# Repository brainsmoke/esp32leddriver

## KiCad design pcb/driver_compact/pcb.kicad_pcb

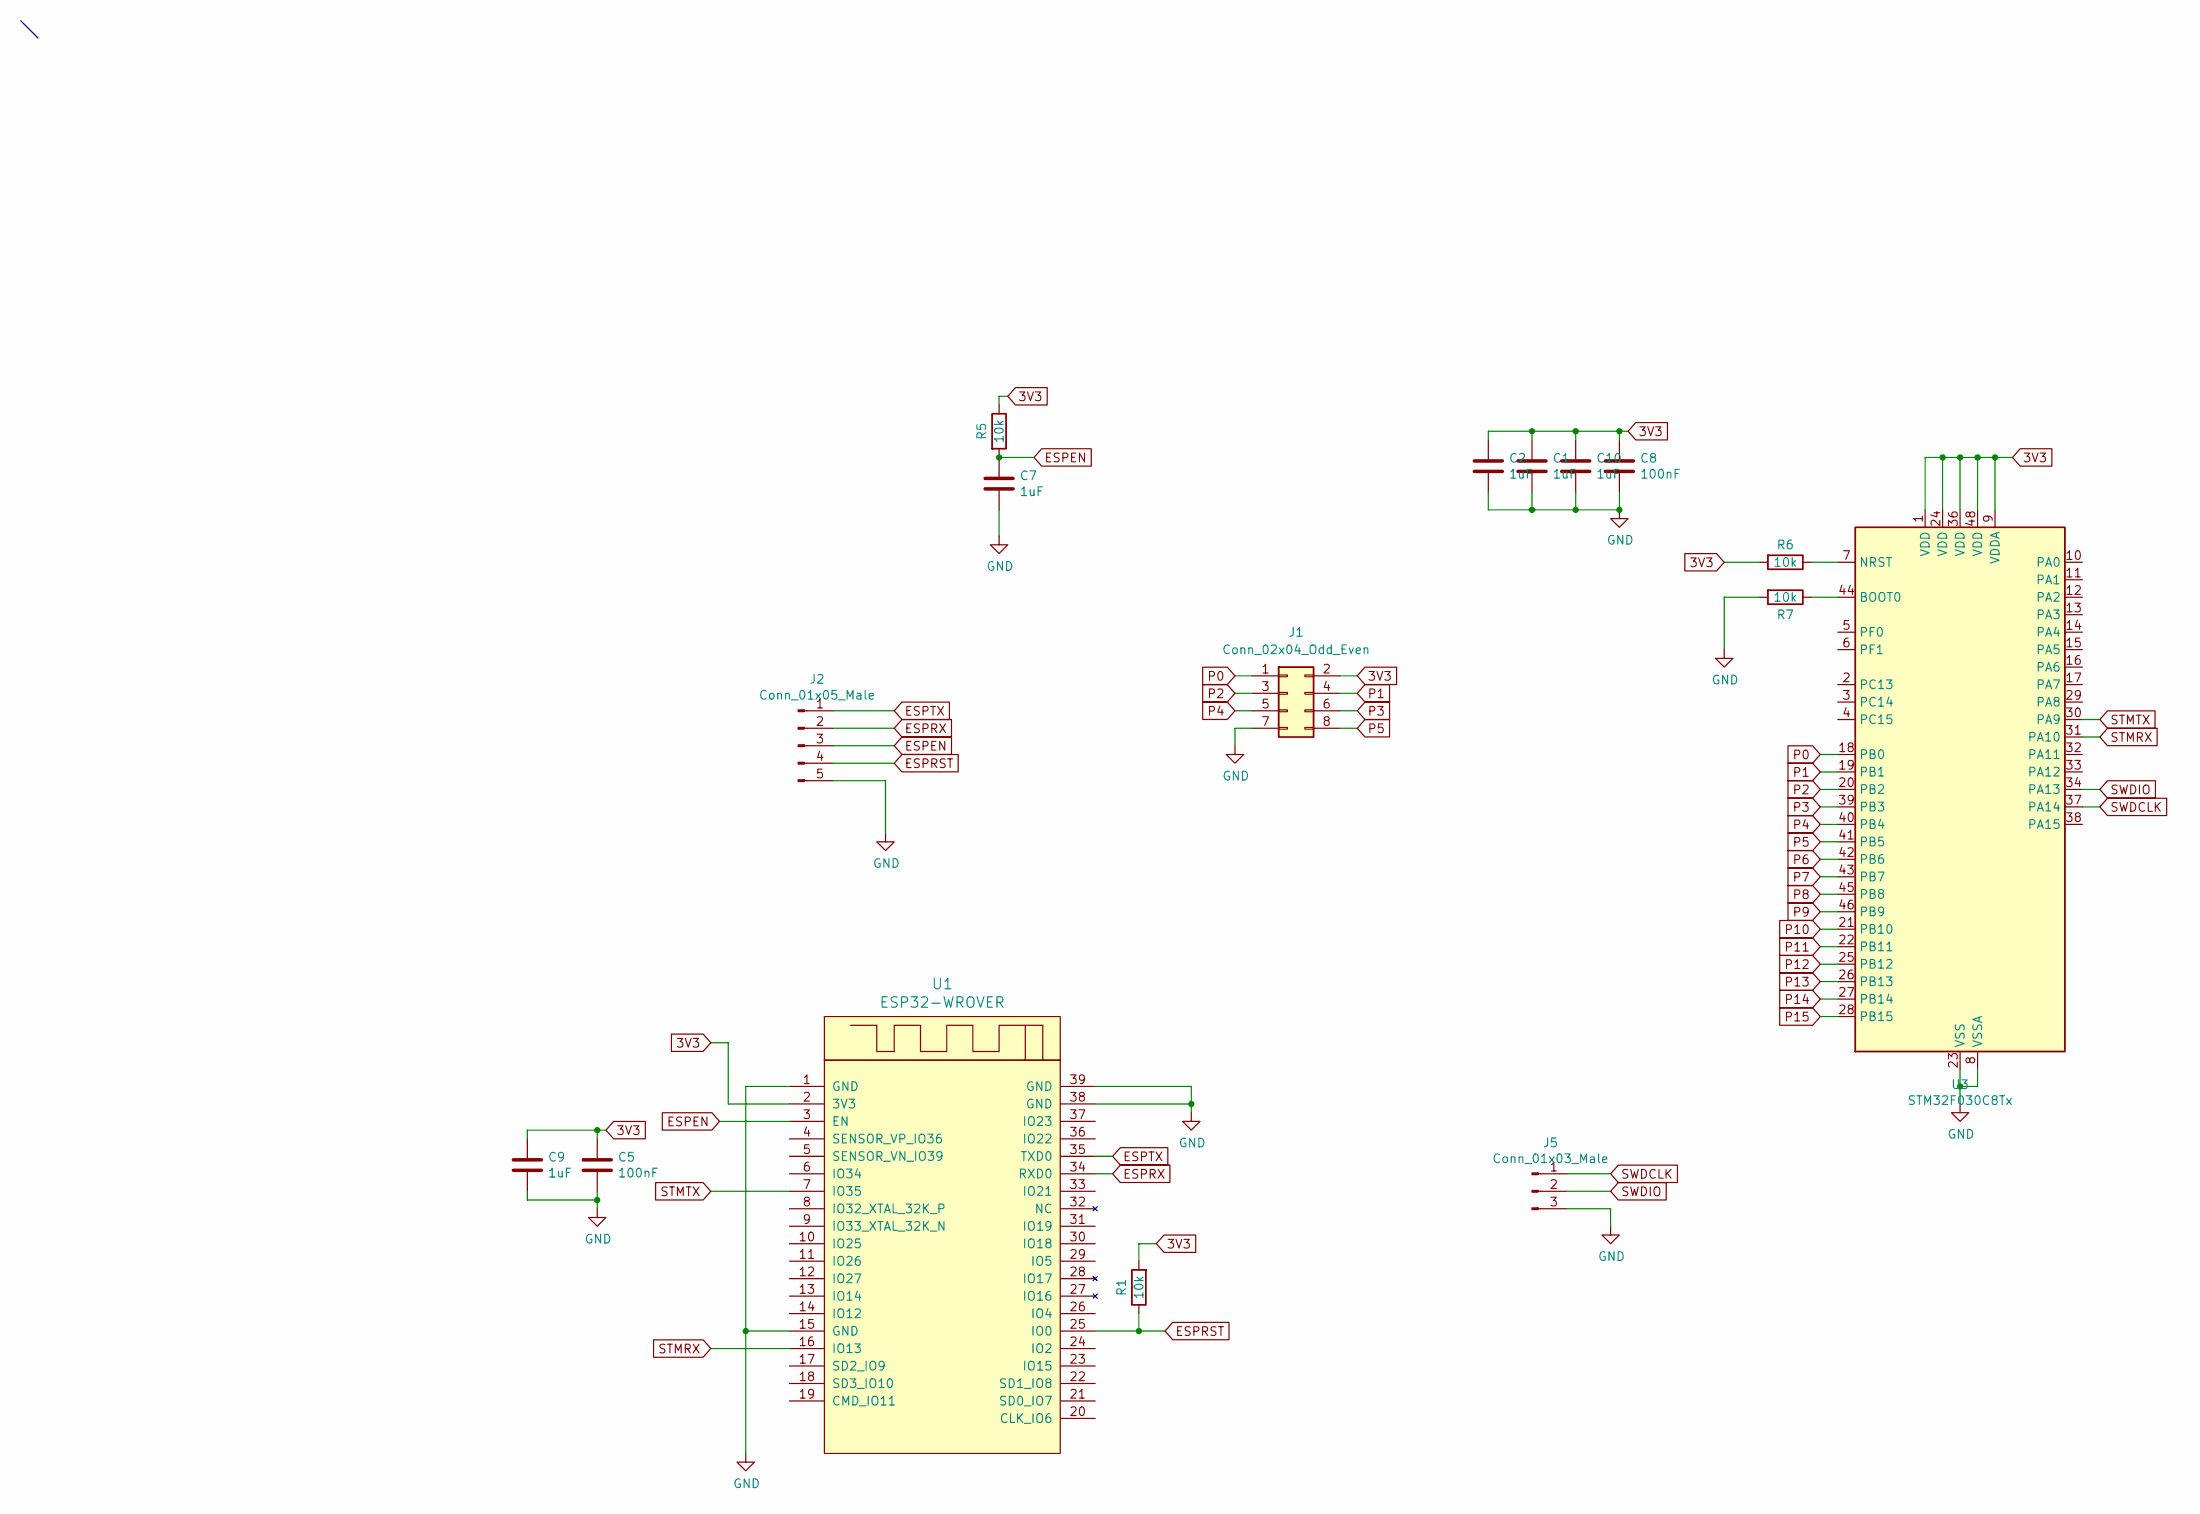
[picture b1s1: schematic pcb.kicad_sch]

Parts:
C1, C2, C7, C9, C10: 1uF; C_0402_1005Metric; LCSC C52923
C5, C8: 100nF; C_0402_1005Metric; LCSC C1525
J1: Conn_02x04_Odd_Even; PinSocket_2x04_P2.54mm_Vertical
J2: Conn_01x05_Male; Molex_PicoBlade_53261-0571_1x05-1MP_P1.25mm_Horizontal; LCSC C225114
J5: Conn_01x03_Male; PinHeader_1x03_P2.54mm_Vertical
R1, R5, R6, R7: 10k; R_0402_1005Metric; LCSC C25744
U1: ESP32-WROVER; XCVR_ESP32-WROVER; LCSC C701352
U3: STM32F030C8Tx; LQFP-48_7x7mm_P0.5mm; LCSC C23922

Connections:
3V3: C1.1, C2.1, C5.1, C8.1, C9.1, C10.1, J1.2, R1.2, R5.1, R6.2, U1.2 (3V3), U3.1 (VDD), U3.9 (VDDA), U3.24 (VDD), U3.36 (VDD), U3.48 (VDD)
ESPEN: C7.1, J2.3, R5.2, U1.3 (EN)
ESPRST: J2.4, R1.1, U1.25 (IO0)
ESPRX: J2.2, U1.34 (RXD0)
ESPTX: J2.1, U1.35 (TXD0)
GND: C1.2, C2.2, C5.2, C7.2, C8.2, C9.2, C10.2, J1.7, J2.5, J5.3, R7.2, U1.1 (GND), U1.15 (GND), U1.38 (GND), U1.39 (GND), U3.8 (VSSA), U3.23 (VSS), U3.35 (VSS), U3.47 (VSS)
unnamed: R7.1, U3.44 (BOOT0)
unnamed: R6.1, U3.7 (NRST)
P0: J1.1, U3.18 (PB0)
P1: J1.4, U3.19 (PB1)
P2: J1.3, U3.20 (PB2)
P3: J1.6, U3.39 (PB3)
P4: J1.5, U3.40 (PB4)
P5: J1.8, U3.41 (PB5)
P6: U3.42 (PB6)
P7: U3.43 (PB7)
P8: U3.45 (PB8)
P9: U3.46 (PB9)
P10: U3.21 (PB10)
P11: U3.22 (PB11)
P12: U3.25 (PB12)
P13: U3.26 (PB13)
P14: U3.27 (PB14)
P15: U3.28 (PB15)
STMRX: U1.16 (IO13), U3.31 (PA10)
STMTX: U1.7 (IO35), U3.30 (PA9)
SWDCLK: J5.1, U3.37 (PA14)
SWDIO: J5.2, U3.34 (PA13)

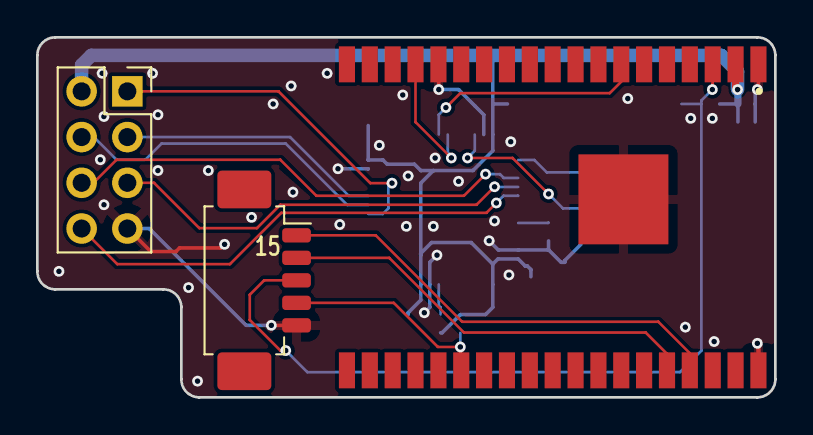
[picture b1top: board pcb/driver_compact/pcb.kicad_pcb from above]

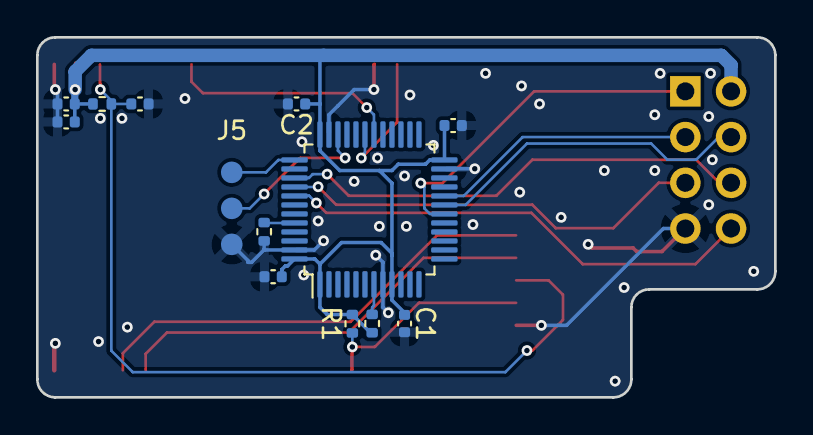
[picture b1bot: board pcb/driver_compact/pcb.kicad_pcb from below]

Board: 4 copper layers, 41.0 x 20.0 mm, 16 parts (13 on the bottom side), 18 nets.

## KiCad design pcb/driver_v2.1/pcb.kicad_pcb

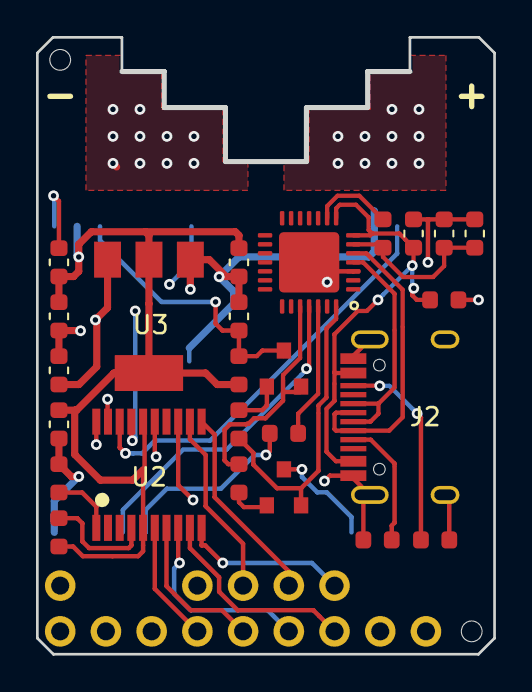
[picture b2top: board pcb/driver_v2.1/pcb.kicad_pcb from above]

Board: 4 copper layers, 25.4 x 34.3 mm, 29 parts (1 on the bottom side), 33 nets.

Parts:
C1, C6, C7: 1uF; C_0603_1608Metric
C2, C4, C9: 10uF; C_0603_1608Metric
C3, C5, C8: 100nF; C_0603_1608Metric
J1: Conn_01x08_Male; PinHeader_1x08_P2.54mm_Vertical
J2: USB_C_Receptacle_USB2.0; USB_C_Receptacle_HRO_TYPE-C-31-M-12
J3: Conn_01x04_Male; PinHeader_1x04_P2.54mm_Vertical
J4: Conn_01x02_Male; PinHeader_1x02_P2.54mm_Vertical
Q1, Q2: AO3400; SOT-23
R1: 1k; R_0603_1608Metric_nolabel
R2, R3, R4, R5, R6, R7: 10k; R_0603_1608Metric_nolabel
R8, R9: 5.1k; R_0603_1608Metric_nolabel
R10: 0Ohm; R_0603_1608Metric_nolabel
U1: ESP32-WROVER; XCVR_ESP32-WROVER
U2: STM32F030F4Px; TSSOP-20_4.4x6.5mm_P0.65mm
U3: AMS1117-3.3; SOT-223-3_TabPin2
U4: CP2102N-Axx-xQFN28; QFN-28-1EP_5x5mm_P0.5mm_EP3.35x3.35mm

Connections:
3V3: C4.1, C5.1, C8.1, C9.1, R5.1, R6.2, U1.2 (3V3), U2.5 (VDDA), U2.16 (VDD), U3.2 (VO)
+5V: C2.1, J1.7, J1.8, R10.2, U3.3 (VI)
ESPEN: C7.1, Q1.3 (D), R5.2, U1.3 (EN)
ESPRST: Q2.3 (D), U1.25 (IO0)
ESPRX: R1.1, U1.34 (RXD0)
ESPTX: U1.35 (TXD0), U4.25 (RXD)
GND: C1.2, C2.2, C3.2, C4.2, C5.2, C6.2, C7.2, C8.2, C9.2, J1.1, J1.2, J2.A1 (GND), J2.A12 (GND), J2.B1 (GND), J2.B12 (GND), J2.S1 (SHIELD), R7.2, R8.1, R9.1, U1.1 (GND), U1.15 (GND), U1.38 (GND), U1.39 (GND), U2.15 (VSS), U3.1 (GND), U4.3 (GND), U4.29 (GND)
unnamed: J1.3, U2.6 (PA0)
unnamed: J1.4, U2.7 (PA1)
unnamed: J1.5, U2.8 (PA2)
unnamed: J1.6, U2.9 (PA3)
unnamed: J2.A5 (CC1), R8.2
unnamed: J2.B5 (CC2), R9.2
unnamed: J3.1, U2.13 (PA7)
unnamed: J3.2, U2.12 (PA6)
unnamed: J3.3, U2.11 (PA5)
unnamed: J3.4, U2.10 (PA4)
unnamed: Q1.1 (G), R3.1
unnamed: Q1.2 (S), R4.2, U4.24 (~RTS)
unnamed: Q2.1 (G), R4.1
unnamed: Q2.2 (S), R3.2, U4.28 (~DTR)
unnamed: R7.1, U2.1 (BOOT0)
unnamed: R6.1, U2.4 (NRST)
unnamed: J2.A6 (D+), J2.B6 (D+), U4.4 (D+)
unnamed: J2.A7 (D-), J2.B7 (D-), U4.5 (D-)
unnamed: R1.2, U4.26 (TXD)
unnamed: C1.1, J2.A4 (VBUS), J2.A9 (VBUS), J2.B4 (VBUS), J2.B9 (VBUS), R10.1, U4.7 (VREGIN), U4.8 (VBUS)
unnamed: R2.2, U4.9 (~RST)
STMRX: U1.16 (IO13), U2.18 (PA10)
STMTX: U1.7 (IO35), U2.17 (PA9)
SWDCLK: J4.2, U2.20 (PA14)
SWDIO: J4.1, U2.19 (PA13)
VIO: C3.1, C6.1, R2.1, U4.6 (VDD)

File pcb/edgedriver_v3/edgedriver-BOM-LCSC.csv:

Comment,Designator,Footprint,LCSC Part Number
"10uF","C4,C2,C9","0603","C19702"
"1uF","C7,C6,C1","0603","C15849"
"100nF","C8,C5,C3","0603","C14663"
"AO3400","Q1,Q2","SOT-23-3L","C20917"
"1k","R1","0603","C21190"
"10k","R6,R7,R3,R4,R5,R2","0603","C25804"
"STM32F030F4P6","U2","TSSOP-20_4.4x6.5x0.65P","C89040"
"AMS1117-3.3","U3","SOT-223","C6186"
"CP2104","U4","QFN-24_EP_4.0x4.0x0.5P","C47742"

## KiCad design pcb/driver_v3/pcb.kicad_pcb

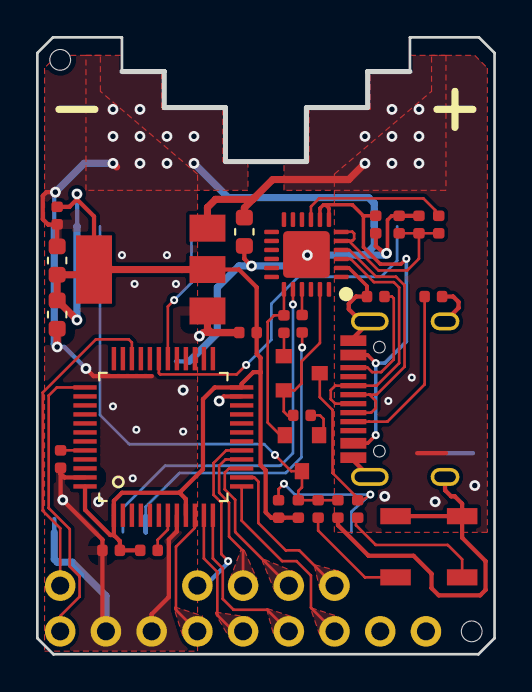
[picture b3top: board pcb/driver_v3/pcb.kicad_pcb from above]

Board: 4 copper layers, 25.4 x 34.3 mm, 34 parts (1 on the bottom side), 35 nets.

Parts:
C1, C6, C7: 1uF; C_0402_1005Metric
C2, C4, C9: 10uF; C_0603_1608Metric
C3, C5, C8, C10: 100nF; C_0402_1005Metric
J1: Conn_01x08_Male; PinHeader_1x08_P2.54mm_Vertical
J2: USB_C_Receptacle_USB2.0; USB_C_Receptacle_HRO_TYPE-C-31-M-12
J3: Conn_01x04_Male; PinHeader_1x04_P2.54mm_Vertical
J4: Conn_01x02_Male; PinHeader_1x02_P2.54mm_Vertical
Q1, Q2: AO3400; SOT-23
R1: 1k; R_0402_1005Metric
R2, R3, R4, R5, R6, R7, R11: 10k; R_0402_1005Metric
R8, R9: 5.1k; R_0402_1005Metric
R10, R12: 470 Ohm; R_0402_1005Metric
SW1, SW2: SW_SPST; SW_SPST_B3U-1000P
U1: ESP32-WROVER; XCVR_ESP32-WROVER
U2: STM32F030C8Tx; LQFP-48_7x7mm_P0.5mm
U3: AMS1117-3.3; SOT-223-3_TabPin2
U4: CP2104; QFN-24-1EP_4x4mm_P0.5mm_EP2.6x2.6mm

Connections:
3V3: C4.1, C5.1, C8.1, C9.1, C10.1, R5.1, R6.2, R11.1, U1.2 (3V3), U2.1 (VDD), U2.9 (VDDA), U2.24 (VDD), U2.48 (VDD), U3.2 (VO)
+5V: C2.1, J1.7, J1.8, U3.3 (VI)
ESPEN: C7.1, Q1.3 (D), R5.2, R10.1, U1.3 (EN)
ESPRST: Q2.3 (D), R11.2, R12.1, U1.25 (IO0)
ESPRX: R1.1, U1.34 (RXD0)
ESPTX: U1.35 (TXD0), U4.20 (RXD)
GND: C1.2, C2.2, C3.2, C4.2, C5.2, C6.2, C7.2, C8.2, C9.2, C10.2, J1.1, J1.2, J2.A1 (GND), J2.A12 (GND), J2.B1 (GND), J2.B12 (GND), J2.S1 (SHIELD), R7.2, R8.1, R9.1, SW1.2 (B), SW2.2 (B), U1.1 (GND), U1.15 (GND), U1.38 (GND), U1.39 (GND), U2.8 (VSSA), U2.23 (VSS), U2.47 (VSS), U3.1 (GND), U4.2 (GND), U4.25 (GND)
unnamed: J1.3, U2.10 (PA0)
unnamed: J1.4, U2.11 (PA1)
unnamed: J1.5, U2.12 (PA2)
unnamed: J1.6, U2.13 (PA3)
unnamed: J2.A5 (CC1), R8.2
unnamed: J2.B5 (CC2), R9.2
unnamed: J3.1, U2.17 (PA7)
unnamed: J3.2, U2.16 (PA6)
unnamed: J3.3, U2.15 (PA5)
unnamed: J3.4, U2.14 (PA4)
unnamed: Q1.1 (G), R3.1
unnamed: Q1.2 (S), R4.2, U4.19 (~RTS)
unnamed: Q2.1 (G), R4.1
unnamed: Q2.2 (S), R3.2, U4.23 (~DTR)
unnamed: R10.2, SW1.1 (A)
unnamed: R12.2, SW2.1 (A)
unnamed: R7.1, U2.44 (BOOT0)
unnamed: R6.1, U2.7 (NRST)
unnamed: J2.A6 (D+), J2.B6 (D+), U4.3 (D+)
unnamed: J2.A7 (D-), J2.B7 (D-), U4.4 (D-)
unnamed: C1.1, J2.A4 (VBUS), J2.A9 (VBUS), J2.B4 (VBUS), J2.B9 (VBUS), U4.7 (REGIN), U4.8 (VBUS)
unnamed: R1.2, U4.21 (TXD)
unnamed: R2.2, U4.9 (~RST)
STMRX: U1.16 (IO13), U2.31 (PA10)
STMTX: U1.7 (IO35), U2.30 (PA9)
SWDCLK: J4.2, U2.37 (PA14)
SWDIO: J4.1, U2.34 (PA13)
VIO: C3.1, C6.1, R2.1, U4.5 (VIO), U4.6 (VDD)

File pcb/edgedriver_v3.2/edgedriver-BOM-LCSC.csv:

Comment,Designator,Footprint,LCSC Part Number
"10uF","C4,C2,C9","0603","C19702"
"1uF","C7,C6,C1","0402","C52923"
"100nF","C8,C5,C3,C10","0402","C1525"
"USB_C_Receptacle_USB2.0","J2","TYPE-C-31_L8.94_W7.3","C165948"
"AO3400","Q1,Q2","SOT-23-3L","C20917"
"1k","R1","0402","C11702"
"470 Ohm","R10,R12","0402","C25167"
"10k","R6,R7,R3,R4,R5,R2,R11","0402","C25744"
"5.1k","R8,R9","0402","C25905"
"SW_SPST","SW1,SW2","Button_Switch_SMD:SW_Push_1P1T_NO_CK_KMR2","C318893"
"STM32F030C8T6","U2","LQFP-48_7.0x7.0x0.5P","C23922"
"AMS1117-3.3","U3","SOT-223","C6186"
"CH9102F","U4","QFN-24_L4.0-W4.0-P0.50EP2.8","C2858418"

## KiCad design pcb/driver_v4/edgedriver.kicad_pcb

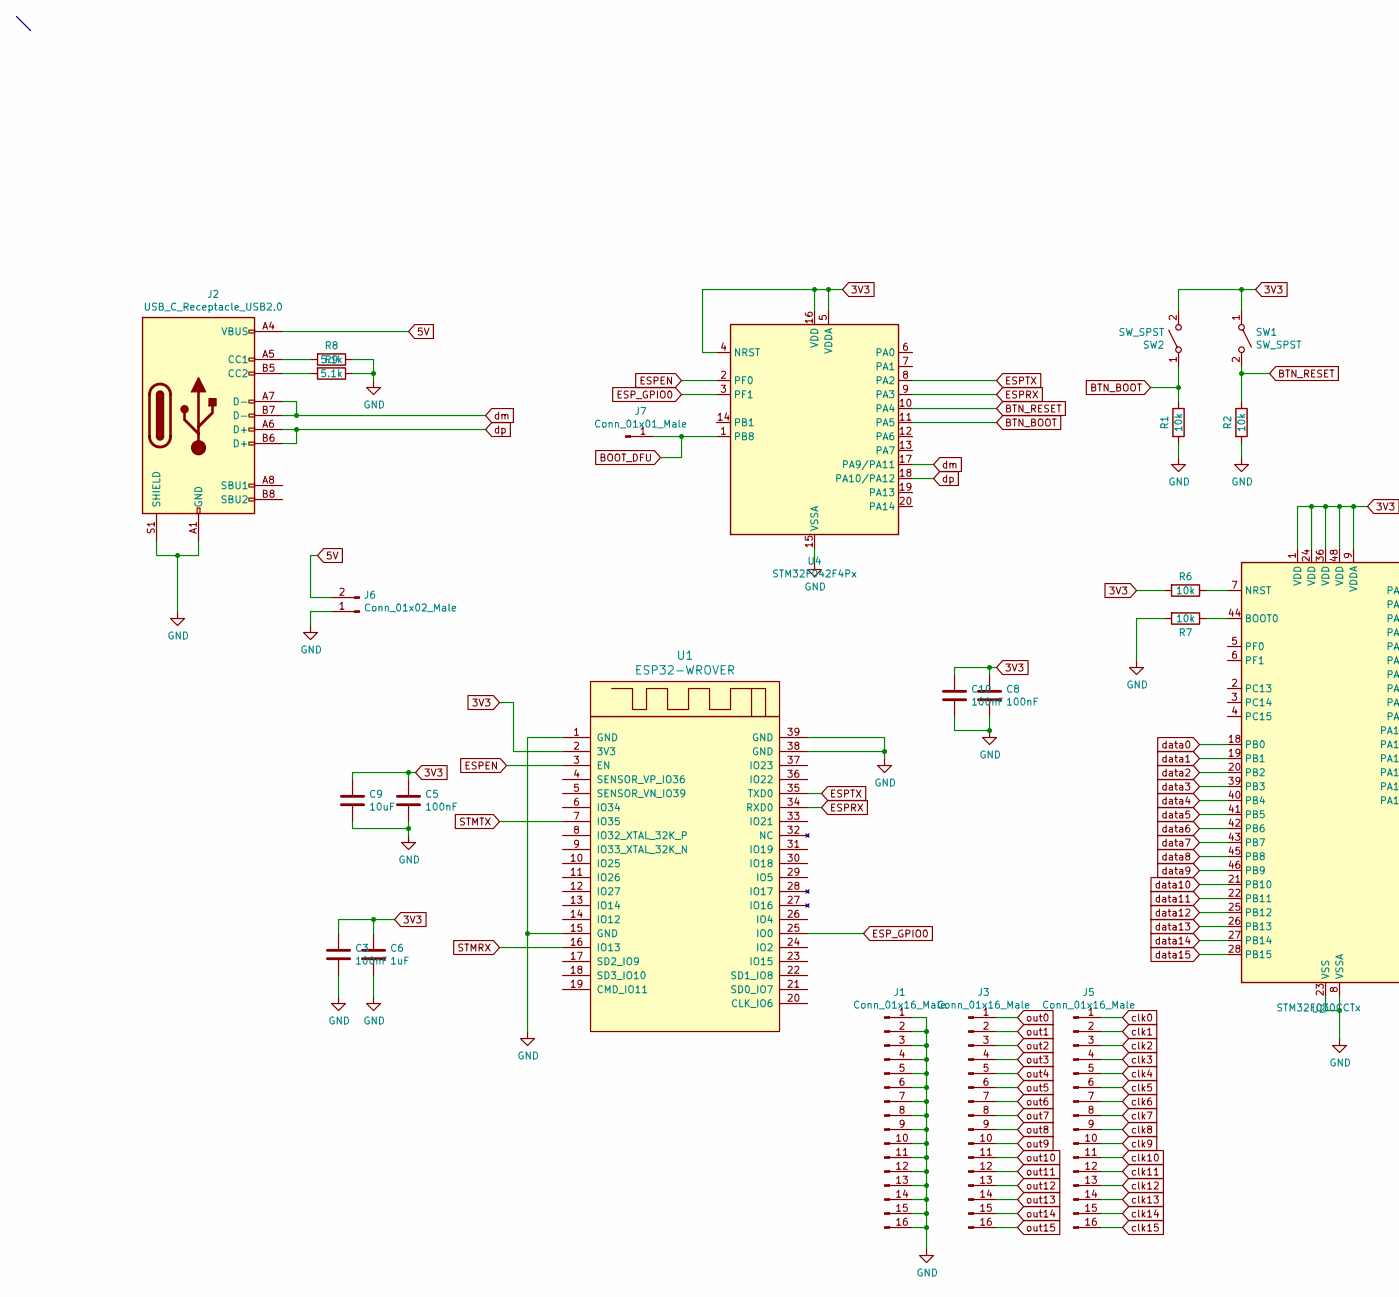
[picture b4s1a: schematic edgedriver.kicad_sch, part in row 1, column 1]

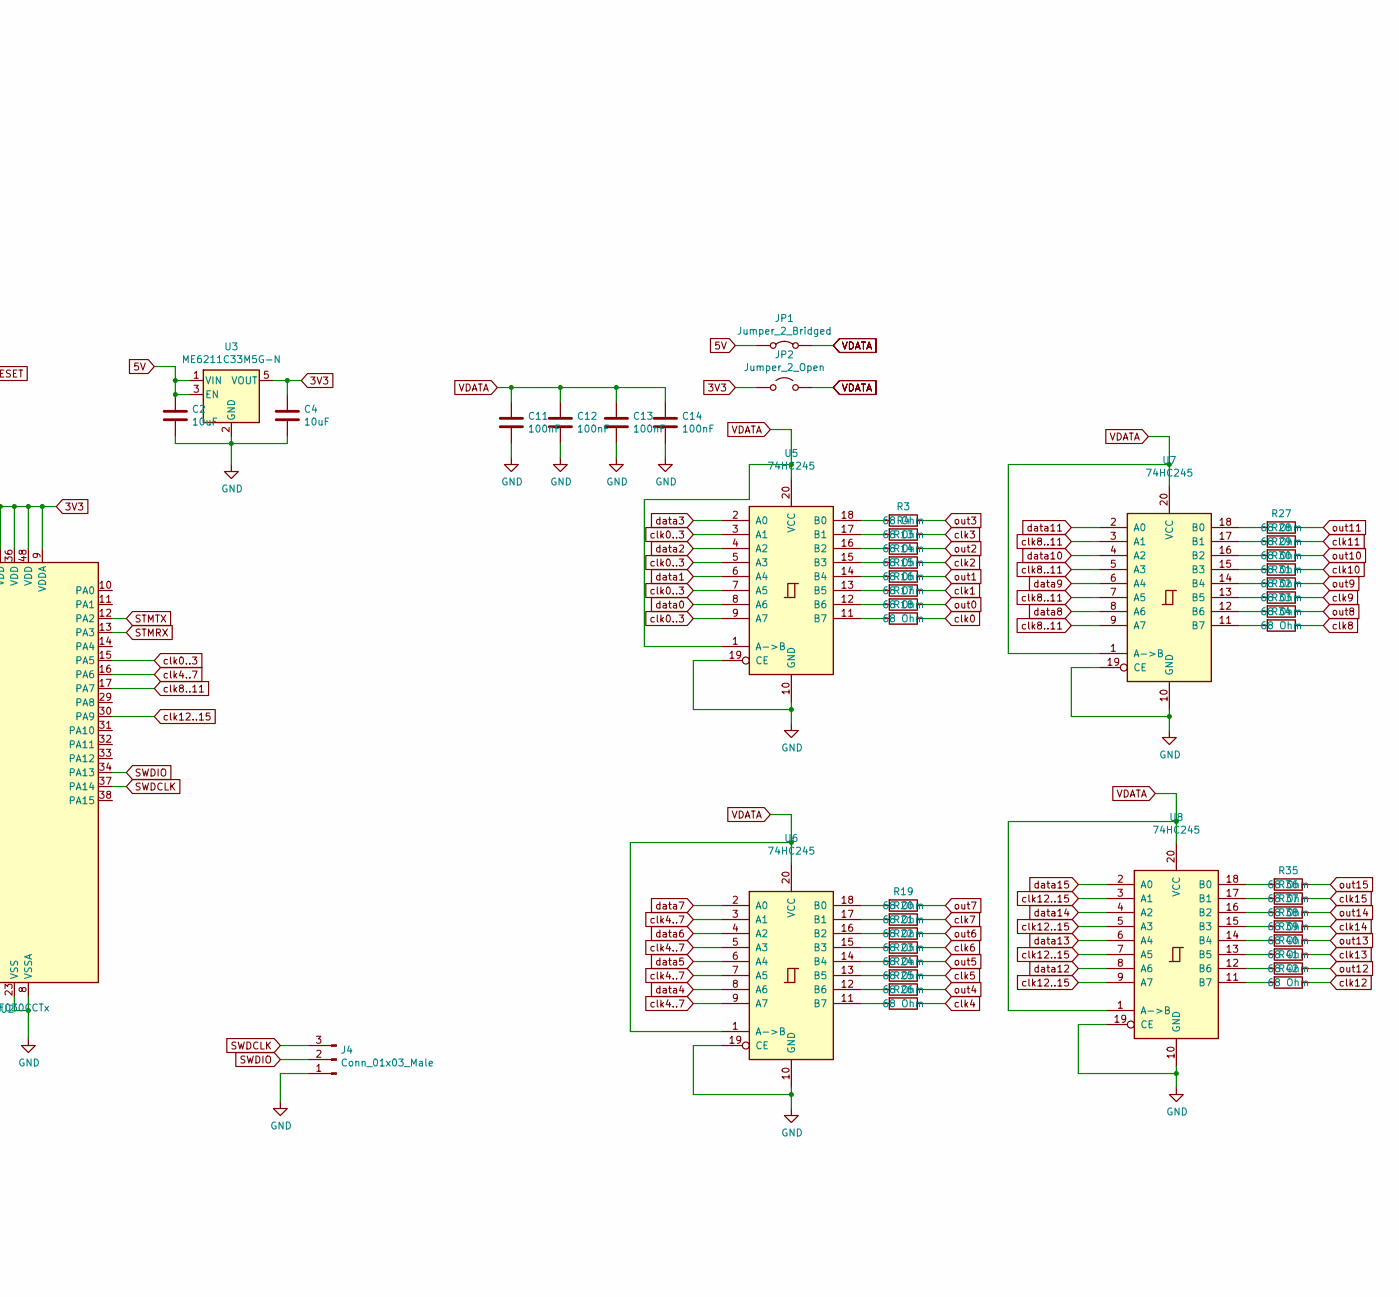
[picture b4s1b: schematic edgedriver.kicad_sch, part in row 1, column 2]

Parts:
C2, C4, C9: 10uF; C_0603_1608Metric; LCSC C19702
C3, C5, C8, C10: 100nF; C_0402_1005Metric; LCSC C1525
C6: 1uF; C_0402_1005Metric; LCSC C52923
C11, C12, C13, C14: 100nF; C_0402_1005Metric; LCSC C19702
J1, J3, J5: Conn_01x16_Male; PinHeader_1x16_P2.54mm_Vertical
J2: USB_C_Receptacle_USB2.0; USB_C_Receptacle_HRO_TYPE-C-31-M-12; LCSC C165948
J4: Conn_01x03_Male; PinHeader_1x03_P2.54mm_Vertical
J6: Conn_01x02_Male; PinHeader_1x02_P2.54mm_Vertical
J7: Conn_01x01_Male; PinHeader_1x01_P2.54mm_Vertical
JP1: Jumper_2_Bridged; SolderJumper-2_P1.3mm_Bridged_Pad1.0x1.5mm
JP2: Jumper_2_Open; SolderJumper-2_P1.3mm_Open_Pad1.0x1.5mm
R1, R2, R6, R7: 10k; R_0402_1005Metric; LCSC C25744
R3, R4, R13, R14, R15, R16, R17, R18, R19, R20, R21, R22, R23, R24, R25, R26, R27, R28, R29, R30, R31, R32, R33, R34, R35, R36, R37, R38, R39, R40, R41, R42: 68 Ohm; R_0402_1005Metric; LCSC C25744
R8, R9: 5.1k; R_0402_1005Metric; LCSC C25905
SW1, SW2: SW_SPST; SW_Push_1P1T_NO_CK_KMR2; LCSC C318893
U1: ESP32-WROVER; XCVR_ESP32-WROVER
U2: STM32F030CCTx; LQFP-48_7x7mm_P0.5mm
U3: ME6211C33M5G-N; SOT-23-5; LCSC C82942
U4: STM32F042F4Px; TSSOP-20_4.4x6.5mm_P0.65mm
U5, U6, U7, U8: 74HC245; TSSOP-20_4.4x6.5mm_P0.65mm

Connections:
3V3: C3.1, C4.1, C5.1, C6.1, C8.1, C9.1, C10.1, JP2.1 (A), R6.2, SW1.1 (A), SW2.2 (B), U1.2 (3V3), U2.1 (VDD), U2.9 (VDDA), U2.24 (VDD), U2.36 (VDD), U2.48 (VDD), U3.5 (VOUT), U4.4 (NRST), U4.5 (VDDA), U4.16 (VDD)
5V: C2.1, J2.A4 (VBUS), J2.A9 (VBUS), J2.B4 (VBUS), J2.B9 (VBUS), J6.2, JP1.1 (A), U3.1 (VIN), U3.3 (EN)
BOOT_DFU: J7.1, U4.1 (PB8)
BTN_BOOT: R1.1, SW2.1 (A), U4.11 (PA5)
BTN_RESET: R2.1, SW1.2 (B), U4.10 (PA4)
ESPEN: U1.3 (EN), U4.2 (PF0)
ESPRX: U1.34 (RXD0), U4.9 (PA3)
ESPTX: U1.35 (TXD0), U4.8 (PA2)
ESP_GPIO0: U1.25 (IO0), U4.3 (PF1)
GND: C2.2, C3.2, C4.2, C5.2, C6.2, C8.2, C9.2, C10.2, C11.2, C12.2, C13.2, C14.2, J1.1, J1.2, J1.3, J1.4, J1.5, J1.6, J1.7, J1.8, J1.9, J1.10, J1.11, J1.12, J1.13, J1.14, J1.15, J1.16, J2.A1 (GND), J2.A12 (GND), J2.B1 (GND), J2.B12 (GND), J2.S1 (SHIELD), J4.1, J6.1, R1.2, R2.2, R7.2, R8.1, R9.1, U1.1 (GND), U1.15 (GND), U1.38 (GND), U1.39 (GND), U2.8 (VSSA), U2.23 (VSS), U2.35 (VSS), U2.47 (VSS), U3.2 (GND), U4.15 (VSSA), U5.10 (GND), U5.19 (CE), U6.10 (GND), U6.19 (CE), U7.10 (GND), U7.19 (CE), U8.10 (GND), U8.19 (CE)
unnamed: J2.A5 (CC1), R8.2
unnamed: J2.B5 (CC2), R9.2
unnamed: R7.1, U2.44 (BOOT0)
unnamed: R6.1, U2.7 (NRST)
unnamed: R3.2, U5.18 (B0)
unnamed: R4.2, U5.17 (B1)
unnamed: R13.2, U5.16 (B2)
unnamed: R14.2, U5.15 (B3)
unnamed: R15.2, U5.14 (B4)
unnamed: R16.2, U5.13 (B5)
unnamed: R17.2, U5.12 (B6)
unnamed: R18.2, U5.11 (B7)
unnamed: R19.2, U6.18 (B0)
unnamed: R20.2, U6.17 (B1)
unnamed: R21.2, U6.16 (B2)
unnamed: R22.2, U6.15 (B3)
unnamed: R23.2, U6.14 (B4)
unnamed: R24.2, U6.13 (B5)
unnamed: R25.2, U6.12 (B6)
unnamed: R26.2, U6.11 (B7)
unnamed: R27.2, U7.18 (B0)
unnamed: R28.2, U7.17 (B1)
unnamed: R29.2, U7.16 (B2)
unnamed: R30.2, U7.15 (B3)
unnamed: R31.2, U7.14 (B4)
unnamed: R32.2, U7.13 (B5)
unnamed: R33.2, U7.12 (B6)
unnamed: R34.2, U7.11 (B7)
unnamed: R35.2, U8.18 (B0)
unnamed: R36.2, U8.17 (B1)
unnamed: R37.2, U8.16 (B2)
unnamed: R38.2, U8.15 (B3)
unnamed: R39.2, U8.14 (B4)
unnamed: R40.2, U8.13 (B5)
unnamed: R41.2, U8.12 (B6)
unnamed: R42.2, U8.11 (B7)
STMRX: U1.16 (IO13), U2.13 (PA3)
STMTX: U1.7 (IO35), U2.12 (PA2)
SWDCLK: J4.3, U2.37 (PA14)
SWDIO: J4.2, U2.34 (PA13)
VDATA: C11.1, C12.1, C13.1, C14.1, JP1.2 (B), JP2.2 (B), U5.1 (A->B), U5.20 (VCC), U6.1 (A->B), U6.20 (VCC), U7.1 (A->B), U7.20 (VCC), U8.1 (A->B), U8.20 (VCC)
clk0: J5.1, R18.1
clk0..3: U2.15 (PA5), U5.3 (A1), U5.5 (A3), U5.7 (A5), U5.9 (A7)
clk1: J5.2, R16.1
clk2: J5.3, R14.1
clk3: J5.4, R4.1
clk4: J5.5, R26.1
clk4..7: U2.16 (PA6), U6.3 (A1), U6.5 (A3), U6.7 (A5), U6.9 (A7)
clk5: J5.6, R24.1
clk6: J5.7, R22.1
clk7: J5.8, R20.1
clk8: J5.9, R34.1
clk8..11: U2.17 (PA7), U7.3 (A1), U7.5 (A3), U7.7 (A5), U7.9 (A7)
clk9: J5.10, R32.1
clk10: J5.11, R30.1
clk11: J5.12, R28.1
clk12: J5.13, R42.1
clk12..15: U2.30 (PA9), U8.3 (A1), U8.5 (A3), U8.7 (A5), U8.9 (A7)
clk13: J5.14, R40.1
clk14: J5.15, R38.1
clk15: J5.16, R36.1
data0: U2.18 (PB0), U5.8 (A6)
data1: U2.19 (PB1), U5.6 (A4)
data2: U2.20 (PB2), U5.4 (A2)
data3: U2.39 (PB3), U5.2 (A0)
data4: U2.40 (PB4), U6.8 (A6)
data5: U2.41 (PB5), U6.6 (A4)
data6: U2.42 (PB6), U6.4 (A2)
data7: U2.43 (PB7), U6.2 (A0)
data8: U2.45 (PB8), U7.8 (A6)
data9: U2.46 (PB9), U7.6 (A4)
data10: U2.21 (PB10), U7.4 (A2)
data11: U2.22 (PB11), U7.2 (A0)
data12: U2.25 (PB12), U8.8 (A6)
data13: U2.26 (PB13), U8.6 (A4)
data14: U2.27 (PB14), U8.4 (A2)
data15: U2.28 (PB15), U8.2 (A0)
dm: J2.A7 (D-), J2.B7 (D-), U4.17 (PA9/PA11)
dp: J2.A6 (D+), J2.B6 (D+), U4.18 (PA10/PA12)
out0: J3.1, R17.1
out1: J3.2, R15.1
out2: J3.3, R13.1
out3: J3.4, R3.1
out4: J3.5, R25.1
out5: J3.6, R23.1
out6: J3.7, R21.1
out7: J3.8, R19.1
out8: J3.9, R33.1
out9: J3.10, R31.1
out10: J3.11, R29.1
out11: J3.12, R27.1
out12: J3.13, R41.1
out13: J3.14, R39.1
out14: J3.15, R37.1
out15: J3.16, R35.1

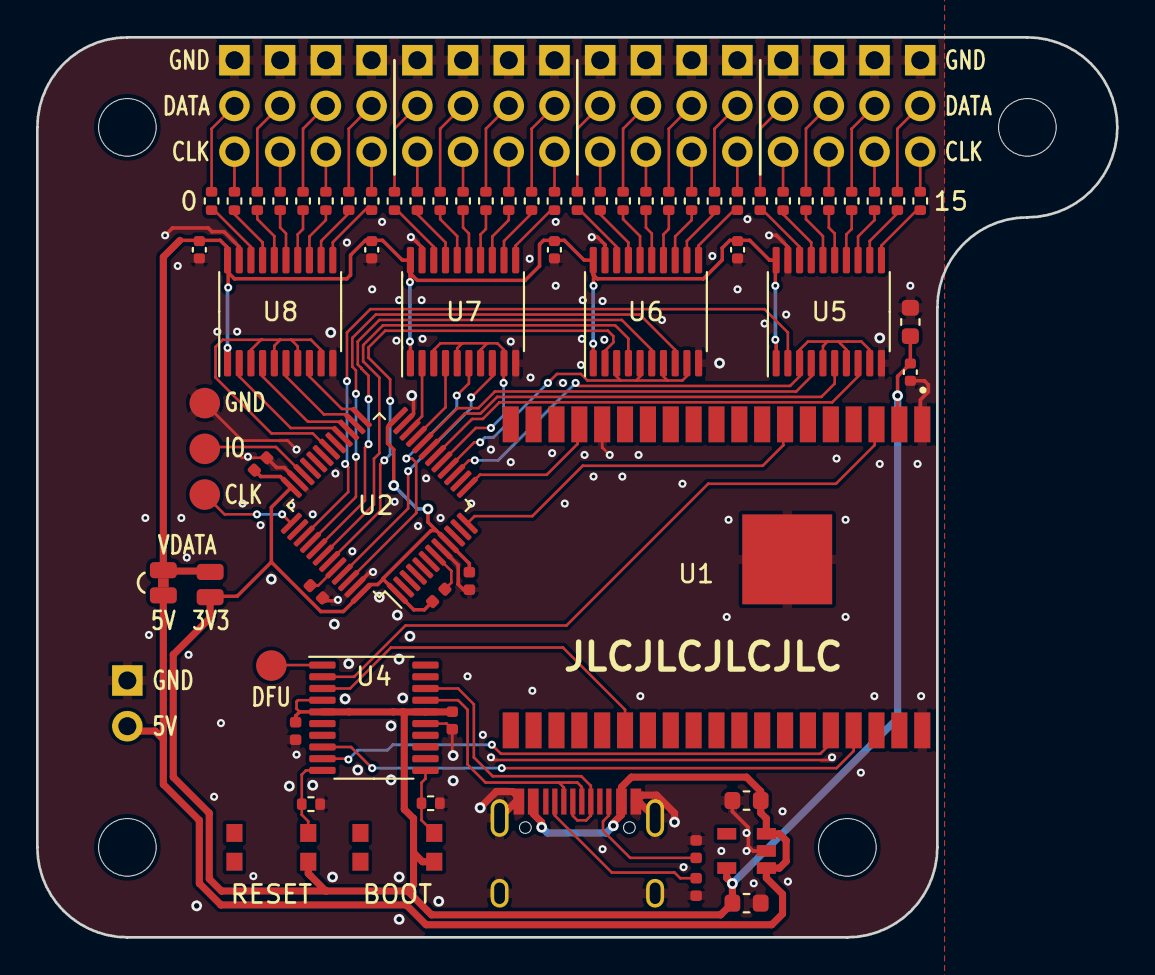
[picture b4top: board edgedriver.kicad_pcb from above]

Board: 2 copper layers, 60.0 x 50.0 mm, 69 parts (0 on the bottom side), 105 nets.
